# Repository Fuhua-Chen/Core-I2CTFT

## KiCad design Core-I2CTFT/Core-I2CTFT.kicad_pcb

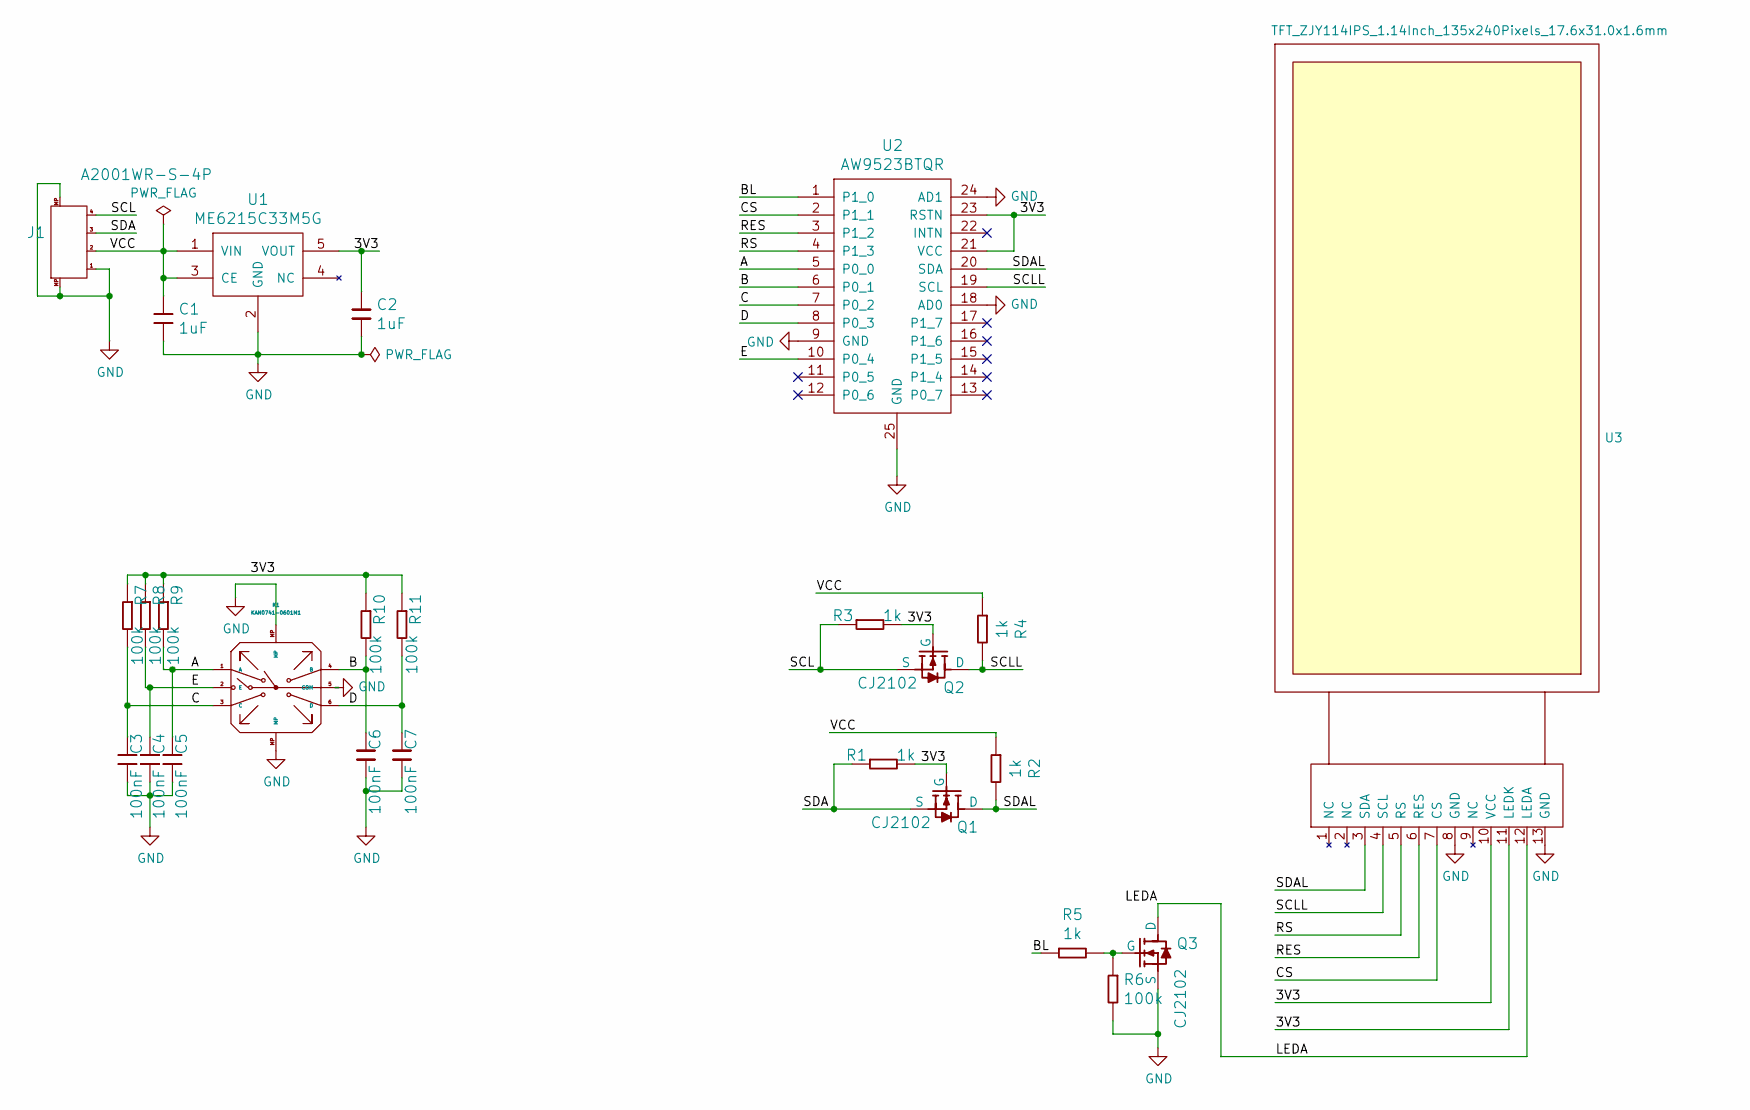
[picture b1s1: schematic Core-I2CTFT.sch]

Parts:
C1, C2: 1uF; C_0603_1608Metric; PartNumber 0603B105K500NT
C3, C4, C5, C6, C7: 100nF; C_0402_1005Metric; PartNumber 0402B104K500NT
J1: A2001WR-S-4P; Connector_CJT_A2001WR-S-4P_1x04-1MP_P2.00mm_Horizontal; PartNumber A2001WR-S-4P
K1: KAN0741-0601M1; Switch_GANGYUAN_KAN0741-0601M1_TACT-SWITCH_8P_7.5x7.5x6mm; PartNumber KAN0741-0601M1
Q1, Q2, Q3: CJ2102; SOT-323_SC-70; PartNumber CJ2102
R1, R2, R3, R4, R5: 1k; R_0402_1005Metric; PartNumber 0402WGF1001TCE
R6, R7, R8, R9, R10, R11: 100k; R_0402_1005Metric; PartNumber 0402WGF1003TCE
U1: ME6215C33M5G; SOT-23-5; PartNumber ME6215C33M5G
U2: AW9523BTQR; QFN-24-1EP_4x4mm_P0.5mm_EP2.7x2.7mm; PartNumber AW9523BTQR
U3: TFT_ZJY114IPS_1.14Inch_135x240Pixels_17.6x31.0x1.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; TFT_ZJY114IPS_1.14Inch_135x240Pixels_17.6x31.0x1.6mm; PartNumber ZJY114IPS

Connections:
/3V3: C2.1, Q1.1 (G), Q2.1 (G), R1.2, R3.2, R7.1, R8.1, R9.1, R10.1, R11.1, U1.5 (VOUT), U2.21 (VCC), U2.23 (RSTN), U3.10 (VCC), U3.11 (LEDK)
/A: C5.1, K1.1 (A), R9.2, U2.5 (P0_0)
/B: C6.1, K1.4 (B), R10.2, U2.6 (P0_1)
/BL: R5.1, U2.1 (P1_0)
/C: C3.1, K1.3 (C), R7.2, U2.7 (P0_2)
/CS: U2.2 (P1_1), U3.7 (CS)
/D: C7.1, K1.6 (D), R11.2, U2.8 (P0_3)
/E: C4.1, K1.2 (E), R8.2, U2.10 (P0_4)
/LEDA: Q3.3 (D), U3.12 (LEDA)
/RES: U2.3 (P1_2), U3.6 (RES)
/RS: U2.4 (P1_3), U3.5 (RS)
/SCL: J1.4, Q2.2 (S), R3.1
/SCLL: Q2.3 (D), R4.2, U2.19 (SCL), U3.4 (SCL)
/SDA: J1.3, Q1.2 (S), R1.1
/SDAL: Q1.3 (D), R2.2, U2.20 (SDA), U3.3 (SDA)
/VCC: C1.1, J1.2, R2.1, R4.1, U1.1 (VIN), U1.3 (CE)
GND: C1.2, C2.2, C3.2, C4.2, C5.2, C6.2, C7.2, J1.1, J1.MP, K1.5 (COM), K1.MP, Q3.2 (S), R6.2, U1.2 (GND), U2.9 (GND), U2.18 (AD0), U2.24 (AD1), U2.25 (GND), U3.8 (GND), U3.13 (GND)
unnamed: Q3.1 (G), R5.2, R6.1

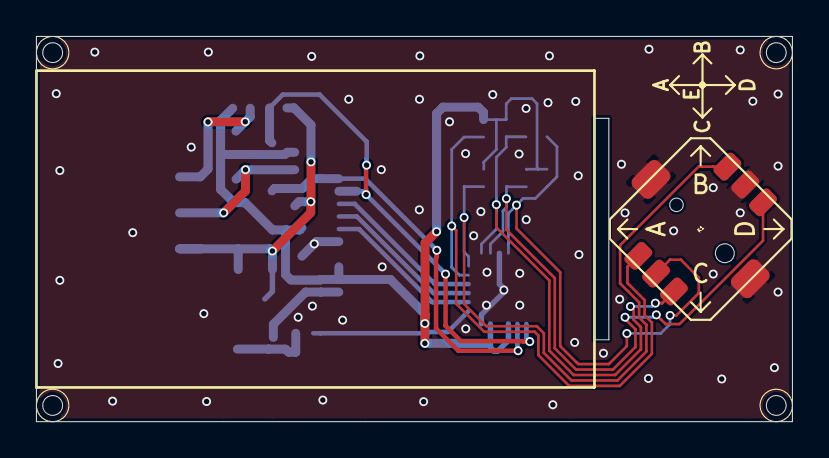
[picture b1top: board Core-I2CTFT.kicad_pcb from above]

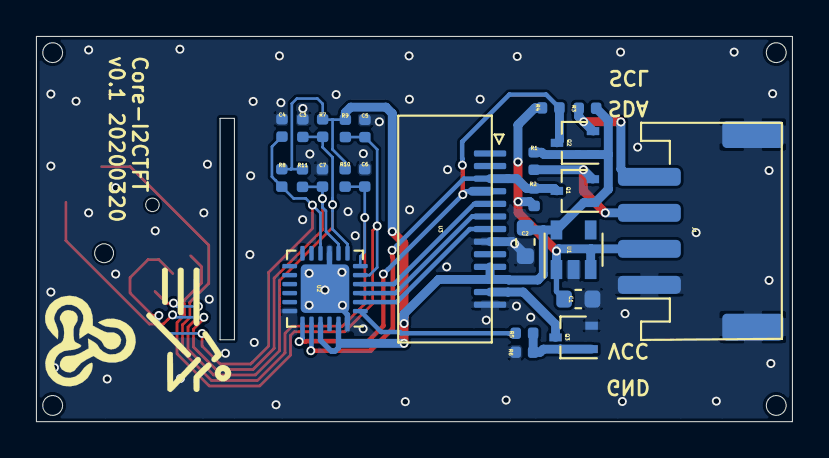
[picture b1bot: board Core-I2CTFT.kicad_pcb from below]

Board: 2 copper layers, 42.0 x 21.4 mm, 26 parts (24 on the bottom side), 18 nets.

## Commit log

2020-03-20 v0.1
